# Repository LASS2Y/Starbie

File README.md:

# Starbie

A tiny motion-controlled digital pet, basically a desktop Tamagotchi. Totally not a Starboy.

Starbie lives on a small PCB built around a Seeed Studio XIAO ESP32-C3. It shows its face and mood on a 0.96" OLED screen, reacts when you tilt or shake it thanks to an MPU6050 accelerometer/gyroscope, notices the temperature and humidity of the room with a DHT11, and you interact with it through two mechanical Cherry MX keys.

This is my starter project for Hack Club's **Half Life** PCB design program.

## How it works

- **Brain:** the XIAO ESP32-C3 runs the firmware and drives everything.
- **Screen:** the SSD1306 128x64 OLED shares an I2C bus with the MPU6050.
- **Motion:** the MPU6050 detects tilts, shakes and taps. That's how you play with Starbie.
- **Environment:** the DHT11 measures temperature and humidity, so Starbie can tell when it's too hot or too cold.
- **Buttons:** two Cherry MX switches for feeding, playing and navigating menus.
- **Power:** USB-C through the XIAO.

## Pinout

| XIAO pin | Connected to |
|---|---|
| D1 | DHT11 data (10 kΩ pull-up to 3.3V) |
| D2 | SW1 (to GND) |
| D3 | SW2 (to GND) |
| D4 / SDA | OLED + MPU6050 SDA |
| D5 / SCL | OLED + MPU6050 SCL |
| 3V3 | OLED, MPU6050, DHT11 |
| GND | Common ground |

The buttons pull the pin to GND when pressed, so the firmware uses the ESP32's internal pull-ups.

## Bill of materials

| Ref | Part | Qty |
|---|---|---|
| U2 | Seeed Studio XIAO ESP32-C3 | 1 |
| J2 | 0.96" SSD1306 OLED, 128x64, I2C | 1 |
| J1 | GY-521 MPU6050 module (1x08 header) | 1 |
| U1 | DHT11 temperature & humidity sensor | 1 |
| SW1, SW2 | Cherry MX switch + DSA keycap | 2 |
| R1 | 10 kΩ resistor (THT) | 1 |

## Repository layout

```
Starbie.kicad_pro     KiCad project
Starbie.kicad_sch     Schematic
Starbie.kicad_pcb     PCB layout
Week 1 Care Package/  Symbols, footprints and 3D models used by the project
firmware/             Firmware (coming soon)
images/               Screenshots (PCB render coming once routing is done)
```

## Status

- [x] Schematic
- [x] Footprints assigned
- [ ] Board outline and component placement
- [ ] Routing
- [ ] 3D render
- [ ] Firmware
- [ ] Fabrication files (Gerbers)

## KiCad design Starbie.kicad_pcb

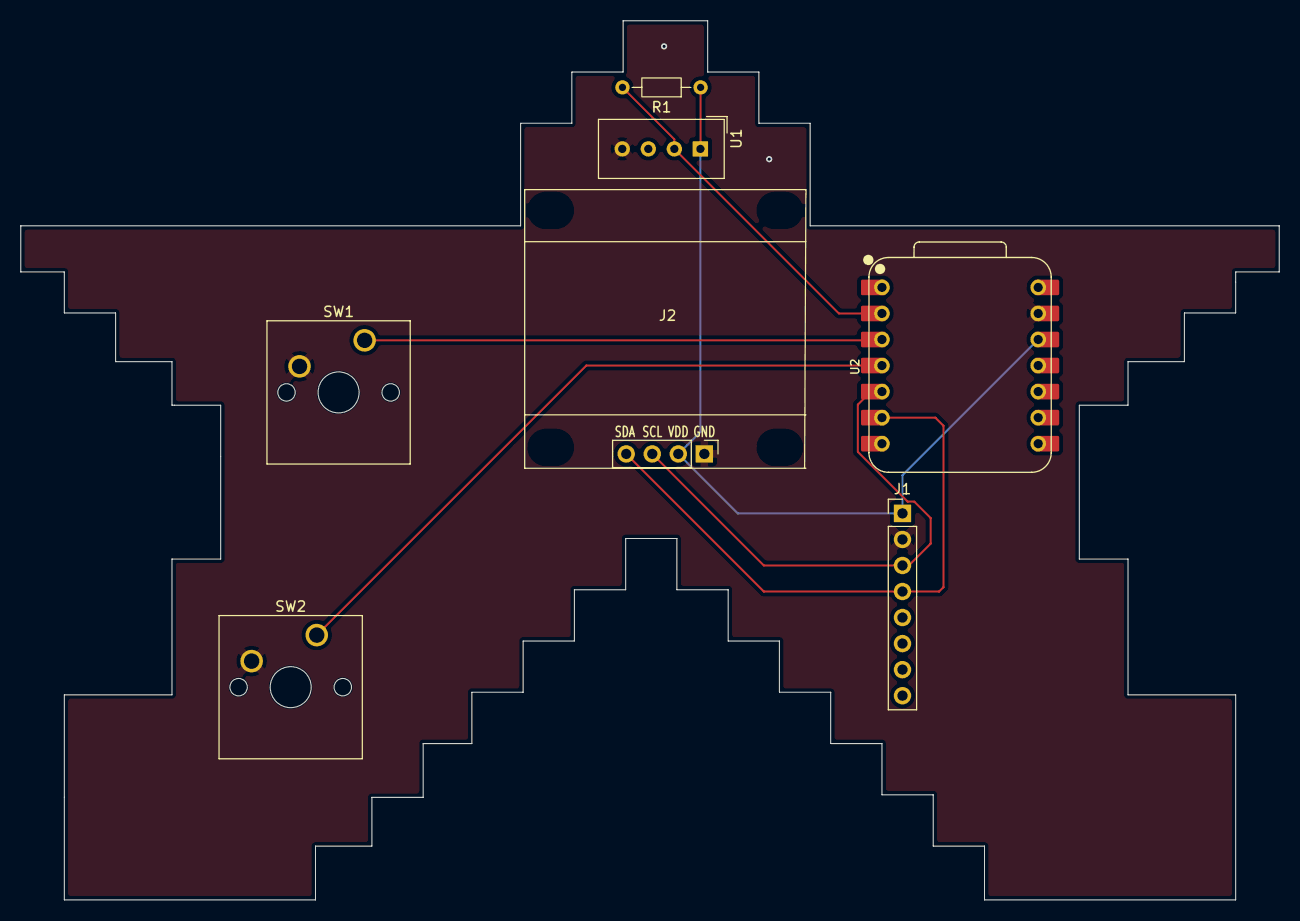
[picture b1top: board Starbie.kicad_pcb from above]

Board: 2 copper layers, 122.8 x 85.8 mm, 7 parts (0 on the bottom side), 7 nets.

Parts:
J1: Conn_01x08_Pin; PinHeader_1x08_P2.54mm_Vertical
J2: Conn_01x04_Pin; Display_128x64_096_I2C
R1: 10K; R_Axial_DIN0204_L3.6mm_D1.6mm_P7.62mm_Horizontal
SW1, SW2: SW_Push; SW_Cherry_MX_1.00u_PCB
U1: DHT11; Aosong_DHT11_5.5x12.0_P2.54mm
U2: XIAO-ESP32-C3-SMD; XIAO-ESP32-C6-DIP

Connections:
+3.3V: J1.1, J2.2, R1.1, U1.1 (VDD), U2.12 (3V3_OUT)
/DHT11 DATA: R1.2, U1.2 (DATA), U2.2 (D1)
/GPIO2: SW1.1, U2.3 (D2)
/GPIO3: SW2.1, U2.4 (D3)
/SCL: J1.3, J2.3, U2.5 (D4)
/SDA: J1.4, J2.4, U2.6 (D5)
GND: J1.2, J2.1, SW1.2, SW2.2, U1.4 (GND), U2.13 (GND)

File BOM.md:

# Starbie — bill of materials

<!-- Generated by Half Life from project cmuv4g8x80dem01smvfayf5wf. Edits here are overwritten on the next sync. -->
<!-- Generated: 2026-10-07T19:32:48.326Z -->

> [!NOTE]
> This parts list is mirrored from [Half Life](https://halflife.hackclub.com). Editing it here will not change the platform's copy, and the next sync overwrites this file.

| Week | Tier | Parts funding |
| --- | --- | --- |
| Week 1 | Tier 1 | $30.00 |

| Part | What it's for | Qty | Unit | Total | Vendor |
| --- | --- | --- | --- | --- | --- |
| Conn_01x08_Pin | — | 1 | $0.00 | $0.00 | — |
| Conn_01x04_Pin | — | 1 | $0.00 | $0.00 | — |
| 10K | — | 1 | $0.00 | $0.00 | — |
| SW_Push | — | 2 | $0.00 | $0.00 | — |
| DHT11 | — | 1 | $0.00 | $0.00 | — |
| XIAO-ESP32-C3-SMD | — | 1 | $0.00 | $0.00 | — |
| **Parts subtotal** | — | — | — | **$0.00** | — |
| **Tax & shipping** | — | — | — | **$0.00** | — |
| **Total** | — | — | — | **$0.00** | — |

$30.00 left of the tier's funding.
